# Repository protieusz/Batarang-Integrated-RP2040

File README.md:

# Batarang-Integrated-RP2040
Batarang keyboard using integrated RP2040 components.

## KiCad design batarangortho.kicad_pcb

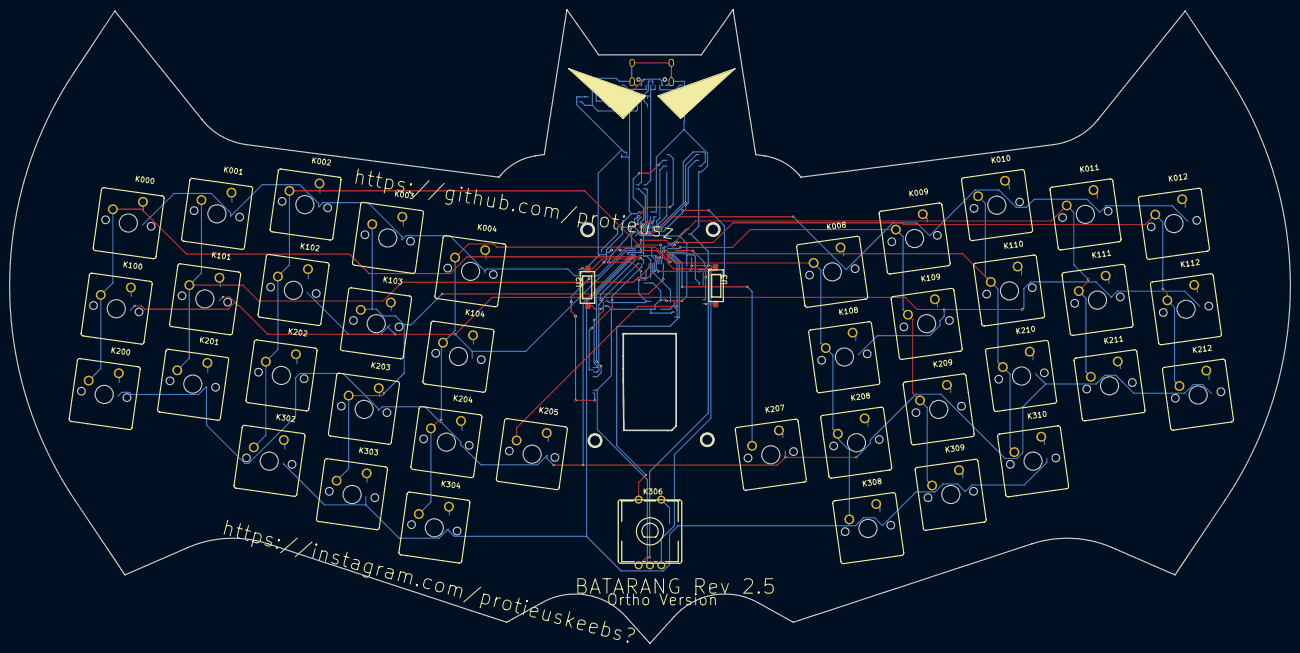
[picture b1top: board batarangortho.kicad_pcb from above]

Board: 2 copper layers, 282.8 x 140.0 mm, 113 parts (0 on the bottom side), 85 nets.

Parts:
C1, C2, C5, C8, C10: 1uF; C0402
C3, C4: 22pF; C0402
C6, C7, C11, C12, C13, C14, C15, C16: 100nF; C0402
C9: 10uF; C0402
D000, D001, D002, D003, D004, D008, D009, D010, D011, D012, D100, D101, D102, D103, D104, D108, D109, D110, D111, D112, D200, D201, D202, D203, D204, D205, D207, D208, D209, D210, D211, D212, D302, D303, D304, D306, D308, D309, D310: SM4007PL; SOD-123F_L2.8-W1.8-LS3.7-RD
D1: PRTR5V0U2X,215; SOT-143_L2.9-W1.3-P1.92-LS2.3-BR
F1: BSMD0805-020-15V; F0805
FPC1: CIRQUE Trackpad; FPC-SMD_FPC05012-09200
K000, K001, K002, K003, K004, K008, K009, K010, K011, K012, K100, K101, K102, K103, K104, K108, K109, K110, K111, K112, K200, K201, K202, K203, K204, K205, K207, K208, K209, K210, K211, K212, K302, K303, K304, K308, K309, K310: 100; CHERRY_MX_100_MILLMAX
K306: PEC11R-4015F-S0024; SW-TH_PEC11R-4XXXF-SXXXX
R1, R2, R3, R6, R7: 5.1kΩ; R0402
R4, R5: 1kΩ; R0402
R8, R9: 27Ω; R0402
U1: XC6206P332MR; SOT-23-3_L2.9-W1.6-P1.90-LS2.8-BR
U2: RESET SWITCH
U3: BOOT SWITCH; RESET SWITCH
U4: W25Q128JVSIQTR; SOIC-8_L5.3-W5.3-P1.27-LS8.0-BL
U5: RP2040; LQFN-56_L7.0-W7.0-P0.4-EP
USBC1: TYPE-C-31-M-12; USB-C_SMD-TYPE-C-31-M-12
X1: 12MHz; OSC-SMD_4P-L3.2-W2.5-BL

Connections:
+1V1: C5.2, C6.2, C7.2, U5.23, U5.45, U5.50
+3V3: C2.2, C8.2, C9.2, C10.2, C11.2, C12.2, C13.2, C14.2, C15.2, C16.2, FPC1.12, R3.2, R6.2, U1.2, U4.8, U5.1, U5.10, U5.22, U5.33, U5.42, U5.43, U5.44, U5.48, U5.49
+5V: C1.2, D1.4, F1.2, U1.3
C4_1: C4.1, R5.1, X1.1
COL0: K000.2, K100.2, K200.2, U5.18
COL1: K001.2, K101.2, K201.2, U5.17
COL2: K002.2, K102.2, K202.2, K302.2, U5.16
COL3: K003.2, K103.2, K203.2, K303.2, U5.15
COL4: K004.2, K104.2, K204.2, K304.2, U5.14
COL5: K205.2, U5.13
COL6: K306.1, U5.12
COL7: K207.2, U5.11
COL8: K008.2, K108.2, K208.2, K308.2, U5.9
COL9: K009.2, K109.2, K209.2, K309.2, U5.8
COL10: K010.2, K110.2, K210.2, K310.2, U5.7
COL11: K011.2, K111.2, K211.2, U5.6
COL12: K012.2, K112.2, K212.2, U5.5
D112_2: D112.2, K112.1
D205_2: D205.2, K205.1
D207_2: D207.2, K207.1
D+: D1.3, R8.2, USBC1.A6, USBC1.B6
D-: D1.2, R9.2, USBC1.A7, USBC1.B7
ENCA: K306.A, U5.37
ENCB: K306.B, U5.36
GND: C1.1, C2.1, C3.1, C4.2, C5.1, C6.1, C7.1, C8.1, C9.1, C10.1, C11.1, C12.1, C13.1, C14.1, C15.1, C16.1, D1.1, FPC1.11, K306.C, R1.1, R2.2, U1.1, U2.1, U3.1, U4.4, U5.19, U5.57, USBC1.0, USBC1.1, USBC1.2, USBC1.3, USBC1.A1, USBC1.A12, USBC1.B1, USBC1.B12, X1.2, X1.4
K000_1: D000.2, K000.1
K001_1: D001.2, K001.1
K002_1: D002.2, K002.1
K003_1: D003.2, K003.1
K004_1: D004.2, K004.1
K008_1: D008.2, K008.1
K009_1: D009.2, K009.1
K010_1: D010.2, K010.1
K011_1: D011.2, K011.1
K012_1: D012.2, K012.1
K100_1: D100.2, K100.1
K101_1: D101.2, K101.1
K102_1: D102.2, K102.1
K103_1: D103.2, K103.1
K104_1: D104.2, K104.1
K108_1: D108.2, K108.1
K109_1: D109.2, K109.1
K110_1: D110.2, K110.1
K111_1: D111.2, K111.1
K200_1: D200.2, K200.1
K201_1: D201.2, K201.1
K202_1: D202.2, K202.1
K203_1: D203.2, K203.1
K204_1: D204.2, K204.1
K208_1: D208.2, K208.1
K209_1: D209.2, K209.1
K210_1: D210.2, K210.1
K211_1: D211.2, K211.1
K212_1: D212.2, K212.1
K302_1: D302.2, K302.1
K303_1: D303.2, K303.1
K304_1: D304.2, K304.1
K306_2: D306.2, K306.2
K308_1: D308.2, K308.1
K309_1: D309.2, K309.1
K310_1: D310.2, K310.1
MISO: FPC1.2, U5.27
MOSI: FPC1.5, U5.30
Q_CLK: U4.6, U5.52
Q_IO0: U4.5, U5.53
Q_IO1: U4.2, U5.55
Q_IO2: U4.3, U5.54
Q_IO3: U4.7, U5.51
Q_SEL: R4.2, R7.1, U4.1, U5.56
R7_2: R6.1, R7.2
RESET: R3.1, U2.2, U5.26
ROW0: D000.1, D001.1, D002.1, D003.1, D004.1, D008.1, D009.1, D010.1, D011.1, D012.1, U5.35
ROW1: D100.1, D101.1, D102.1, D103.1, D104.1, D108.1, D109.1, D110.1, D111.1, D112.1, U5.34
ROW2: D200.1, D201.1, D202.1, D203.1, D204.1, D205.1, D207.1, D208.1, D209.1, D210.1, D211.1, D212.1, U5.32
ROW3: D302.1, D303.1, D304.1, D306.1, D308.1, D309.1, D310.1, U5.31
SCK: FPC1.1, U5.29
SS: FPC1.3, U5.28
U3_2: R4.1, U3.2
U5_46: R9.1, U5.46
U5_47: R8.1, U5.47
USBC1_A5: R2.1, USBC1.A5
USBC1_B5: R1.2, USBC1.B5
VBUS: F1.1, USBC1.A4, USBC1.A9, USBC1.B4, USBC1.B9
XIN: C3.2, U5.20, X1.3
XOUT: R5.2, U5.21

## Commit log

2023-08-31 QMK source code
2023-08-31 Gerbers
2023-08-31 Converted PCB file from EasyEDA json
2023-08-31 Schematic
